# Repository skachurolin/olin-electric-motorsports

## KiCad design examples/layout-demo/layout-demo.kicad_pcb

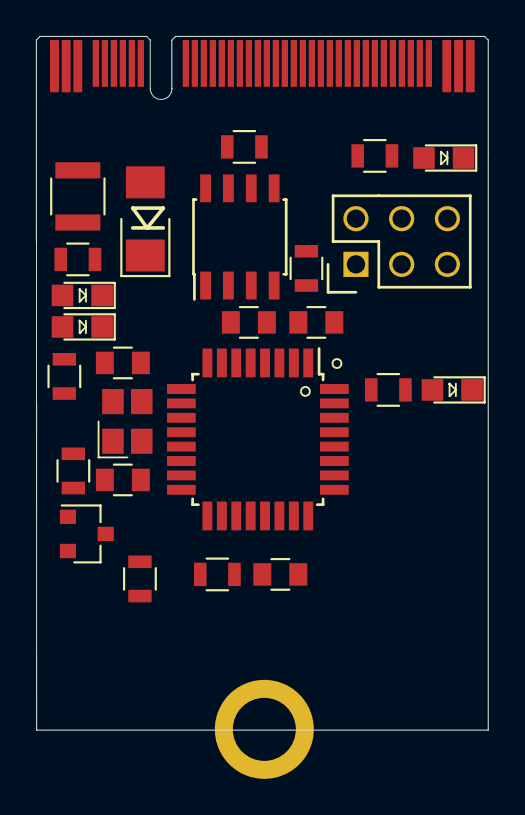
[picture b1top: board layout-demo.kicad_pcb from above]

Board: 2 copper layers, 25.1 x 38.5 mm, 27 parts (0 on the bottom side), 22 nets, no tracks yet.

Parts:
C1, C5: C_0.1uF; C_0805_OEM
C2: C_100pF; C_0805_OEM
C3, C4: C_30pF; C_0805_OEM
D1: D_Zener_18V; DO-214AA
D2, D3, D4, D5: LED_0805; LED_0805_OEM
F1: F_500mA_16V; Fuse_1210
H1: MountingHole_Pad; M.2_Mount
J1: CONN_02X03; Pin_Header_Straight_2x03
J2: M.2_BoardEdge; Automotive_M.2_Edge_Connector
Q1: SSM3K333R; SOT-23F
R1: R_100; R_0805_OEM
R2, R5, R6: R_1K; R_0805_OEM
R3: R_200; R_0805_OEM
R4, R8: R_10K; R_0805_OEM
R7: R_100K; R_0805_OEM
R9: R_120_DNP; R_0805_OEM
U1: ATMEGA16M1; TQFP-32_7x7mm_Pitch0.8mm
U2: MCP2561-E_SN; SOIC-8_3.9x4.9mm_Pitch1.27mm_OEM
Y1: Crystal_SMD; Crystal_SMD_FA238

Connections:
+5V: C1.1, C5.1, J1.2, J2.P38, J2.P39, J2.P40, R1.1, R3.1, R4.1, R8.1, U1.4 (VCC), U2.3 (VDD)
+BATT: F1.2, J2.P3
/BAT_FUSED: D1.1 (K), F1.1, R2.1
/CAN_+: J2.7, R9.1, U2.7 (CANH)
/CAN_-: J2.8, R9.2, U2.6 (CANL)
/CAN_RX: U1.7 ((PCINT11/T1/ICP1B/RXCAN)PC3), U2.4 (RXD)
/CAN_TX: U1.6 ((PCINT10/T0/TXCAN)PC2), U2.1 (TXD)
/DEBUG: R5.1, U1.32 ((PCINT17/CLKO/PSCIN0)PD1)
/MISO: J1.1, U1.1 ((PCINT18/PSCIN2/OC1A/MISO_A)PD2)
/MOSI: J1.4, U1.2 ((PCINT19/TXD/TXLIN/OC0A/~SS/MOSI_A)PD3)
/RESET: J1.5, R4.2, U1.31 ((PCINT24/OCD/~RESET)PE0)
/SCK: J1.3, U1.12 ((PCINT20/ADC1/RXD/RXLIN/ICP1A/SCK_A)PD4)
/SHDN_IN: J2.P1, J2.P2, Q1.1 (G), R6.1, R7.1
/SHDN_SENSE: Q1.3 (D), R8.2, U1.14 ((PCINT22/ADC3/INT0/ACMPN2)PD6)
GND: C1.2, C2.2, C3.2, C4.2, C5.2, D1.2 (A), D2.1 (K), D3.1 (K), D4.1 (K), D5.1 (K), H1.1, J1.6, J2.4, J2.5, J2.6, J2.9, Q1.2 (S), R7.2, U1.5 (GND), U1.20 (AGND), U2.2 (VSS), U2.8 (STBY), Y1.2, Y1.4
unnamed: C2.1, R1.2, U1.19 (AVCC)
unnamed: C3.1, U1.11 ((PCINT26/ADC0/XTAL2)PE2), Y1.1
unnamed: C4.1, U1.10 ((PCINT25/OC0B/XTAL1)PE1), Y1.3
unnamed: D2.2 (A), R2.2
unnamed: D3.2 (A), R3.2
unnamed: D4.2 (A), R5.2
unnamed: D5.2 (A), R6.2

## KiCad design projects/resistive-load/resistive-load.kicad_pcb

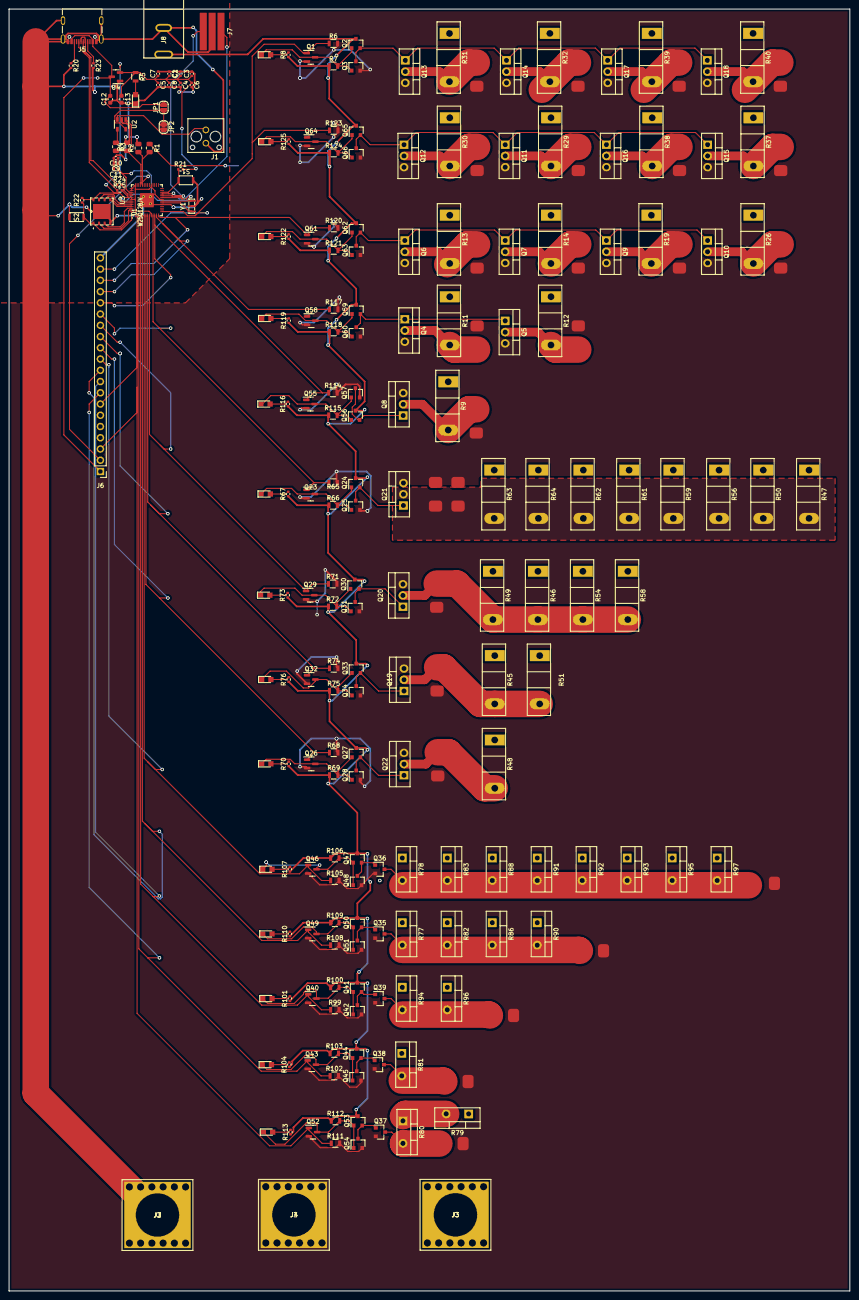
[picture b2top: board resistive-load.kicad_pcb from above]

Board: 2 copper layers, 189.9 x 289.6 mm, 236 parts (0 on the bottom side), 110 nets.

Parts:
C1, C2, C3, C4, C5, C6, C7, C8, C9, C10, C11: C; C_0402_1005Metric
C12, C13: C; C_0603_1608Metric
D1, D2, D3, D4, D5, D6, D7, D8, D9, D10, D11, D12, D13, D14, D15: LED_WHITE; CHIPLED_0805
J1: MicroFit_V_2
J2, J3, J4: redcude_7461166; redcube_7461166
J5: USB4105-GF-A
J6: Conn_01x20; PinHeader_1x20_P2.54mm_Vertical
J7: Conn_01x03; nunchuck_pads
J8: Barrel_jack; barrel_jack_PJ-037A
JP1, JP2: SolderJumper_2_Open; SolderJumper-2_P1.3mm_Open_RoundedPad1.0x1.5mm
Q1, Q23, Q26, Q29, Q32, Q40, Q43, Q46, Q49, Q52, Q55, Q58, Q61, Q64: RK7002BMT116; SOT-23
Q2, Q24, Q27, Q30, Q33, Q41, Q44, Q47, Q50, Q53, Q56, Q59, Q62, Q65: SSM3J334R; SOT-23F
Q3, Q25, Q28, Q31, Q34, Q35, Q36, Q37, Q38, Q39, Q42, Q45, Q48, Q51, Q54, Q57, Q60, Q63, Q66: SSM3K333R; SOT-23F
Q4, Q5, Q6, Q7, Q8, Q9, Q10, Q11, Q12, Q13, Q14, Q15, Q16, Q17, Q18, Q19, Q20, Q21, Q22: PJP45N06A_T0_00001; TO-220-3_Vertical
R1, R2, R3, R4: R; R_0805_2012Metric
R5: R_330; R_0805_OEM
R6, R65, R68, R71, R74, R99, R102, R105, R108, R111, R114, R117, R120, R123: R_10K; R_0805_OEM
R7, R66, R69, R72, R75, R100, R103, R106, R109, R112, R115, R118, R121, R124: R_1K; R_0805_OEM
R8, R20, R21, R22, R23, R24, R25, R67, R70, R73, R76, R101, R104, R107, R110, R113, R116, R119, R122, R125: R; R_0402_1005Metric
R9, R11, R12, R13, R14, R19, R26, R29, R30, R31, R32, R37, R38, R39, R40, R45, R46, R47, R48, R49, R50, R51, R54, R56, R58, R59, R61, R62, R63, R64: 1R2-100W; TO-247-2_Vertical
R10, R15, R16, R17, R18, R27, R28, R33, R34, R35, R36, R41, R42, R43, R44, R52, R53, R55, R57, R60, R84, R85, R87, R89, R98: 0R-20A; Keystone_5102
R77, R78, R79, R80, R81, R82, R83, R86, R88, R90, R91, R92, R93, R94, R95, R96, R97: 8R-20W; TO-220-2_Vertical
S1: RST; KXT321LHS
S2: BOOT; KXT321LHS
U1: W25Q128JV; MIC_WSON-8-L
U2: MCP6001; SOT-23-5_OEM
U3: RP2040
U4: MCP1702T-3302E_CB; SOT-23
Y1: 12MHz; CSTNE

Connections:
+3V3: C1.2, C2.1, C3.1, C4.1, C5.1, C6.1, C7.1, C8.1, C13.1, R5.1, R21.2, R22.2, U1.8 (VDD), U3.1 (IOVDD), U3.10 (IOVDD), U3.22 (IOVDD), U3.33 (IOVDD), U3.42 (IOVDD), U3.43 (ADC_AVDD), U3.44 (VREG_VIN), U3.48 (USB_VDD), U3.49 (IOVDD), U4.2 (VOUT)
+5V: C12.2, J5.A4B9 (VBUS), J5.B4A9 (VBUS), J6.1, JP1.2 (B), U4.3 (VIN)
+12V: J8.1 (center), Q2.3 (D), Q24.3 (D), Q27.3 (D), Q30.3 (D), Q33.3 (D), Q41.3 (D), Q44.3 (D), Q47.3 (D), Q50.3 (D), Q53.3 (D), Q56.3 (D), Q59.3 (D), Q62.3 (D), Q65.3 (D), R7.1, R8.1, R66.1, R67.1, R69.1, R70.1, R72.1, R73.1, R75.1, R76.1, R100.1, R101.1, R103.1, R104.1, R106.1, R107.1, R109.1, R110.1, R112.1, R113.1, R115.1, R116.1, R118.1, R119.1, R121.1, R122.1, R124.1, R125.1
+BATT: J3.1, R1.1, R9.1, R11.1, R12.1, R13.1, R14.1, R19.1, R26.1, R29.1, R30.1, R31.1, R32.1, R37.1, R38.1, R39.1, R40.1, R45.1, R46.1, R47.1, R48.1, R49.1, R50.1, R51.1, R54.1, R56.1, R58.1, R59.1, R61.1, R62.1, R63.1, R64.1, R77.1, R78.1, R79.1, R81.1, R82.1, R83.1, R86.1, R88.1, R90.1, R91.1, R92.1, R93.1, R94.1, R95.1, R96.1, R97.1
/Microcontroller/BOOT: R22.1, S2.2, U1.1 (~CS), U3.56 (~QSPI_CS)
/Microcontroller/GPIO0: J6.3, J6.7, Q52.1 (G), R111.1, U3.2 (GPIO0)
/Microcontroller/GPIO1: J6.8, Q43.1 (G), R102.1, U3.3 (GPIO1)
/Microcontroller/GPIO2: J6.9, Q40.1 (G), R99.1, U3.4 (GPIO2)
/Microcontroller/GPIO3: J6.10, Q49.1 (G), R108.1, U3.5 (GPIO3)
/Microcontroller/GPIO4: J6.11, Q46.1 (G), R105.1, U3.6 (GPIO4)
/Microcontroller/GPIO5: J6.12, Q26.1 (G), R68.1, U3.7 (GPIO5)
/Microcontroller/GPIO6: J6.13, Q32.1 (G), R74.1, U3.8 (GPIO6)
/Microcontroller/GPIO7: J6.14, Q29.1 (G), R71.1, U3.9 (GPIO7)
/Microcontroller/GPIO8: J6.15, Q23.1 (G), R65.1, U3.11 (GPIO8)
/Microcontroller/GPIO9: J6.16, Q55.1 (G), R114.1, U3.12 (GPIO9)
/Microcontroller/GPIO10: J6.17, Q58.1 (G), R117.1, U3.13 (GPIO10)
/Microcontroller/GPIO11: J6.18, Q61.1 (G), R120.1, U3.14 (GPIO11)
/Microcontroller/GPIO12: J6.19, Q1.1 (G), Q64.1 (G), R6.1, R123.1, U3.15 (GPIO12)
/Microcontroller/GPIO26: J6.2, R1.2, R2.1, U3.38 (GPIO26/ADC0)
/Microcontroller/GPIO27: R3.2, R4.1, U2.1, U3.39 (GPIO27/ADC1)
/Microcontroller/RUN: R21.1, S1.2, U3.26 (RUN)
/Microcontroller/SWCLK: J7.1, U3.24 (SWCLK)
/Microcontroller/SWDIO: J7.3, U3.25 (SWDIO)
/Resistor Tree Large/12V Gate Driver10/GATE: Q8.1 (G), Q56.2 (S), Q57.3 (D)
/Resistor Tree Large/12V Gate Driver11/GATE: Q4.1 (G), Q5.1 (G), Q59.2 (S), Q60.3 (D)
/Resistor Tree Large/12V Gate Driver12/GATE: Q6.1 (G), Q7.1 (G), Q9.1 (G), Q10.1 (G), Q62.2 (S), Q63.3 (D)
/Resistor Tree Large/12V Gate Driver13/GATE: Q11.1 (G), Q12.1 (G), Q15.1 (G), Q16.1 (G), Q65.2 (S), Q66.3 (D)
/Resistor Tree Large/12V Gate Driver14/GATE: Q2.2 (S), Q3.3 (D), Q13.1 (G), Q14.1 (G), Q17.1 (G), Q18.1 (G)
/Resistor Tree Medium/12V Gate Driver6/GATE: Q22.1 (G), Q27.2 (S), Q28.3 (D)
/Resistor Tree Medium/12V Gate Driver7/GATE: Q19.1 (G), Q33.2 (S), Q34.3 (D)
/Resistor Tree Medium/12V Gate Driver8/GATE: Q20.1 (G), Q30.2 (S), Q31.3 (D)
/Resistor Tree Medium/12V Gate Driver9/GATE: Q21.1 (G), Q24.2 (S), Q25.3 (D)
/Resistor Tree Small/12V Gate Driver1/GATE: Q39.1 (G), Q41.2 (S), Q42.3 (D)
/Resistor Tree Small/12V Gate Driver2/GATE: Q38.1 (G), Q44.2 (S), Q45.3 (D)
/Resistor Tree Small/12V Gate Driver3/GATE: Q36.1 (G), Q47.2 (S), Q48.3 (D)
/Resistor Tree Small/12V Gate Driver4/GATE: Q35.1 (G), Q50.2 (S), Q51.3 (D)
/Resistor Tree Small/12V Gate Driver5/GATE: Q37.1 (G), Q53.2 (S), Q54.3 (D)
/Vshunt: J1.1, U2.3 (+)
GND: J4.1, Q1.2 (S), Q3.2 (S), Q4.3 (S), Q5.3 (S), Q6.3 (S), Q7.3 (S), Q8.3 (S), Q9.3 (S), Q10.3 (S), Q11.3 (S), Q12.3 (S), Q13.3 (S), Q14.3 (S), Q15.3 (S), Q16.3 (S), Q17.3 (S), Q18.3 (S), Q19.3 (S), Q20.3 (S), Q21.3 (S), Q22.3 (S), Q23.2 (S), Q25.2 (S), Q26.2 (S), Q28.2 (S), Q29.2 (S), Q31.2 (S), Q32.2 (S), Q34.2 (S), Q35.2 (S), Q36.2 (S), Q37.2 (S), Q38.2 (S), Q39.2 (S), Q40.2 (S), Q42.2 (S), Q43.2 (S), Q45.2 (S), Q46.2 (S), Q48.2 (S), Q49.2 (S), Q51.2 (S), Q52.2 (S), Q54.2 (S), Q55.2 (S), Q57.2 (S), Q58.2 (S), Q60.2 (S), Q61.2 (S), Q63.2 (S), Q64.2 (S), Q66.2 (S), R6.2, R10.2, R15.2, R16.2, R17.2, R18.2, R27.2, R28.2, R33.2, R34.2, R35.2, R36.2, R41.2, R42.2, R43.2, R44.2, R52.2, R53.2, R55.2, R57.2, R60.2, R65.2, R68.2, R71.2, R74.2, R84.2, R85.2, R87.2, R89.2, R98.2, R99.2, R102.2, R105.2, R108.2, R111.2, R114.2, R117.2, R120.2, R123.2
GNDA: C1.1, C2.2, C3.2, C4.2, C5.2, C6.2, C7.2, C8.2, C9.2, C10.2, C11.2, C12.1, C13.2, D1.1 (K), J1.2, J2.1, J5.A1B12 (GND), J5.B1A12 (GND), J5.S1 (SHELL), J5.S2 (SHELL), J5.S3 (SHELL), J5.S4 (SHELL), J6.20, J7.2, J8.2 (Shell), R2.2, R4.2, R20.2, R23.2, S1.1, S2.1, U1.4 (GND), U1.9 (EP), U2.2 (V-), U3.19 (TESTEN), U3.57 (GND), U4.1 (GND), Y1.2
unnamed: C9.1, C10.1, C11.1, U3.23 (DVDD), U3.45 (VREG_VOUT), U3.50 (DVDD)
unnamed: D1.2 (A), R5.2
unnamed: D2.1 (K), Q1.3 (D), Q2.1 (G), Q3.1 (G), R7.2
unnamed: D2.2 (A), R8.2
unnamed: D3.1 (K), Q23.3 (D), Q24.1 (G), Q25.1 (G), R66.2
unnamed: D3.2 (A), R67.2
unnamed: D4.1 (K), Q26.3 (D), Q27.1 (G), Q28.1 (G), R69.2
unnamed: D4.2 (A), R70.2
unnamed: D5.1 (K), Q29.3 (D), Q30.1 (G), Q31.1 (G), R72.2
unnamed: D5.2 (A), R73.2
unnamed: D6.1 (K), Q32.3 (D), Q33.1 (G), Q34.1 (G), R75.2
unnamed: D6.2 (A), R76.2
unnamed: D7.1 (K), Q40.3 (D), Q41.1 (G), Q42.1 (G), R100.2
unnamed: D7.2 (A), R101.2
unnamed: D8.1 (K), Q43.3 (D), Q44.1 (G), Q45.1 (G), R103.2
unnamed: D8.2 (A), R104.2
unnamed: D9.1 (K), Q46.3 (D), Q47.1 (G), Q48.1 (G), R106.2
unnamed: D9.2 (A), R107.2
unnamed: D10.1 (K), Q49.3 (D), Q50.1 (G), Q51.1 (G), R109.2
unnamed: D10.2 (A), R110.2
unnamed: D11.1 (K), Q52.3 (D), Q53.1 (G), Q54.1 (G), R112.2
unnamed: D11.2 (A), R113.2
unnamed: D12.1 (K), Q55.3 (D), Q56.1 (G), Q57.1 (G), R115.2
unnamed: D12.2 (A), R116.2
unnamed: D13.1 (K), Q58.3 (D), Q59.1 (G), Q60.1 (G), R118.2
unnamed: D13.2 (A), R119.2
unnamed: D14.1 (K), Q61.3 (D), Q62.1 (G), Q63.1 (G), R121.2
unnamed: D14.2 (A), R122.2
unnamed: D15.1 (K), Q64.3 (D), Q65.1 (G), Q66.1 (G), R124.2
unnamed: D15.2 (A), R125.2
unnamed: J5.A5 (CC1), R23.1
unnamed: J5.A6 (D+), J5.B6 (D+), R25.1
unnamed: J5.A7 (D-), J5.B7 (D-), R24.1
unnamed: J5.B5 (CC2), R20.1
unnamed: Q4.2 (D), R11.2, R15.1
unnamed: Q5.2 (D), R12.2, R16.1
unnamed: Q6.2 (D), R13.2, R17.1
unnamed: Q7.2 (D), R14.2, R18.1
unnamed: Q8.2 (D), R9.2, R10.1
unnamed: Q9.2 (D), R19.2, R27.1
unnamed: Q10.2 (D), R26.2, R28.1
unnamed: Q11.2 (D), R29.2, R33.1
unnamed: Q12.2 (D), R30.2, R34.1
unnamed: Q13.2 (D), R31.2, R35.1
unnamed: Q14.2 (D), R32.2, R36.1
unnamed: Q15.2 (D), R37.2, R41.1
unnamed: Q16.2 (D), R38.2, R42.1
unnamed: Q17.2 (D), R39.2, R43.1
unnamed: Q18.2 (D), R40.2, R44.1
unnamed: Q19.2 (D), R45.2, R51.2, R52.1
unnamed: Q20.2 (D), R46.2, R49.2, R54.2, R55.1, R58.2
unnamed: Q21.2 (D), R47.2, R50.2, R56.2, R57.1, R59.2, R60.1, R61.2, R62.2, R63.2, R64.2
unnamed: Q22.2 (D), R48.2, R53.1
unnamed: Q35.3 (D), R77.2, R82.2, R86.2, R87.1, R90.2
unnamed: Q36.3 (D), R78.2, R83.2, R88.2, R89.1, R91.2, R92.2, R93.2, R95.2, R97.2
unnamed: Q37.3 (D), R80.2, R84.1
unnamed: Q38.3 (D), R81.2, R85.1
unnamed: Q39.3 (D), R94.2, R96.2, R98.1
unnamed: R3.1, U2.4 (-)
unnamed: R24.2, U3.46 (USB_D-)
unnamed: R25.2, U3.47 (USB_D+)
unnamed: R79.2, R80.1
unnamed: U1.2 (DO/IO1), U3.55 (QSPI_SD1)
unnamed: U1.3 (~WP/IO2), U3.54 (QSPI_SD2)
unnamed: U1.5 (DI/IO0), U3.53 (QSPI_SD0)
unnamed: U1.6 (SCK), U3.52 (QSPI_SCLK)
unnamed: U1.7 (~HOLD/IO3), U3.51 (QSPI_SD3)
unnamed: U3.20 (XIN), Y1.1
unnamed: U3.21 (XOUT), Y1.3
VBUS: JP1.1 (A), JP2.1 (A), U2.5 (V+)

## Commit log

2022-05-20 Initial structure for CHARGING state in AIR control
2022-06-03 Initial 29-bit CAN ID support
2022-07-22 revised power distribution tutorial
2022-07-28 feat: support for generating gebers and gerber zip
2022-08-07 fix: tweak kitbot geber settings
2022-11-09 feat: initial schematic for resistive load
2022-11-10 Worked on board
    Resistive network layout
2022-11-15 Add MSB schematic
2022-11-16 Ayo
    Ayo
2022-11-16 fix: update pin assignment for transistors
2022-11-18 Major rev 3
    made edits
2022-11-28 feat: simple schematic and empty layout
2022-11-29 feat: bad floorplan to start with
2022-12-05 CAN testing
2022-12-06 completed stm32 board schematic
2023-03-09 Collecting CAN data
2023-03-09 Dashboard Firmware First Draft
2023-03-18 Updated Dashboard Firmware (post spring break)
2023-03-23 Complete Throttle Firmware First Draft
2023-03-23 Fix compilation errors
2023-03-23 Push throttle BUILD file
2023-03-23 Format bazel BUILD file
2023-03-23 Fix CAN init throttle debug error
2023-03-23 Update CAN Debugging Code
2023-03-23 Update MKVI DBC file to include throttle yml, update throttle BUILD to use MKVI dbc
2023-03-26 Add 4 digit 7-segment display symbol to parts library
2023-03-26 Add digital isolator for SPI to parts library
2023-03-26 Add 6 pin tag connect to parts library
2023-03-26 Add labels to TagConnect, connectors, and DC bus caps
2023-03-26 Add bypass capacitors to 1A LDO
2023-03-26 Complete resistor divider circuit
2023-03-26 Add isolated DCDC converter to parts library
2023-03-26 Add low voltage fuses to 5V and +BATT rails
2023-03-26 Add missing bypass capacitor on ADC VCC pin
2023-03-26 Set up kicad files
2023-03-26 Add 1A 5V LDO to parts library
2023-03-26 Remove TS_5V symbol from parts library
2023-03-26 Add test pads
2023-03-26 Spec DC bus capacitors
2023-03-26 Complete schematic connections for all components
2023-03-26 Replace 5V_TS label with 5V_ISO
2023-03-26 Add 3 position right angle Micro-Fit 3 symbol to library
2023-03-26 Add MAX7221 to parts library
2023-03-26 Add power flags for -TS and +TS
2023-03-26 Tweak 4 digit 7-segment display symbol
2023-03-26 Tweak MAX7221 symbol
2023-03-26 Add supporting components for SPI between ADC and MCU
2023-03-26 Add resistors for resistor divider and DCDC converter to schematic
2023-03-26 Add 2A PTC fuse to parts library
2023-03-26 Remove old components
2023-03-26 Add bypass caps to isolated buck, add 5V_TS power flag
2023-03-26 Fix directories, add initial components for mock inverter
2023-03-26 Add supporting components to ADC
2023-03-26 Add ADC to parts library
2023-03-26 Add fuse MPN and purchasing link to holder symbol
2023-03-26 Change part number on bleed resistors
2023-03-26 Update schematic based on DRC rules
2023-03-26 Move DC bus capacitors before HV fuse
2023-03-26 Add jumper to CAN termination resistor
2023-03-26 Add bleed resistors to DC bus capacitors
2023-03-26 Add LV and HV power LEDs
2023-03-26 Add HV fuse holder to parts library
2023-03-26 Add 3D model of relay
2023-03-26 Clean up schematic
2023-03-26 Fix metadata on 20k resistors
2023-03-26 Add LEDs to programming LEDs
2023-03-26 Resolve conflicts in symbol library
2023-03-26 Resolve conflicts in symbol convert library
2023-03-26 Move TS power LED to unfused side
2023-03-26 Add distinction between TS fused and TS unfused
2023-03-26 Fix ERC errors and annotate schematic
    Manually merging symbols deleted a number of the symbols used in my schematic. I added them back to the library.
2023-03-26 Seperate DC bus capacitors from capacitor charge status
2023-03-26 Replace relay with SPST-NC version
2023-03-26 Add build file
2023-03-26 Obtain clean copy of symbol library from main
2023-03-26 Attempt manual fixes on symbol library when adding one symbol
2023-03-26 Fix library associations for LEDs in schematic
2023-03-26 Attempt manual fixes on symbol library when adding two symbols
2023-03-26 Fix additional symbols in symbol library
2023-03-26 Fix MAX7221 symbol
2023-03-26 Fix fuse symbol
2023-03-26 Fix tag connect symbol
2023-03-30 Comment out btldr lines for testing
2023-03-30 Added firmware functionality, 10 millisecond delay, interrupts, LED logic, and more
2023-04-04 Comment out btldr files for testing
2023-04-04 Formatting, changed CAN message throttle_state to throttle_status
2023-04-05 Refactored by removing STATES_DICTIONARY and incorporating Amit
2023-04-06 Resolve feedback from draft 1
2023-04-06 Snakecased non-constants, fixed callbacks, renamed dashboard to dashboard_message
2023-04-14 implement `kalman_update`, write docstring
2023-04-14 implement `run_kalman`, write docstring
2023-04-19 write computation essay
2023-04-20 Resolve brake implaus logic error
2023-04-20 Change throttle pot names to R an L
2023-04-28 Fix throttle state error
2023-04-28 Send throttle raw positions over CAN for debugging
2023-04-28 Calibrate pot values for RKH
2023-04-28 Report correct throttle status over CAN
2023-05-01 Update MKVI Air control and add in more yml
2023-05-01 Update pins
2023-05-01 Comments
2023-05-01 Update most tests with new HitL code
2023-05-01 Format
2023-05-01 Update AIR code and tests to pass
2023-05-01 Hardcode BTLDR_ID for now
2023-05-01 file structure
2023-05-01 compile
2023-05-01 debugging thangs
2023-05-01 updated code and cleaned up file structure
2023-05-01 Addressed review comments and fixed bugs.
2023-05-01 formatting
2023-05-01 snake case
2023-05-01 more directory things
2023-05-01 formatting x3
2023-05-01 added test folder and .py file
2023-05-01 updated bspd.yml to properly reflect messages + corrected slice lengths
2023-05-01 directory update
2023-07-19 Add files via upload
    Adding dashboard and can_test for the dashboard
